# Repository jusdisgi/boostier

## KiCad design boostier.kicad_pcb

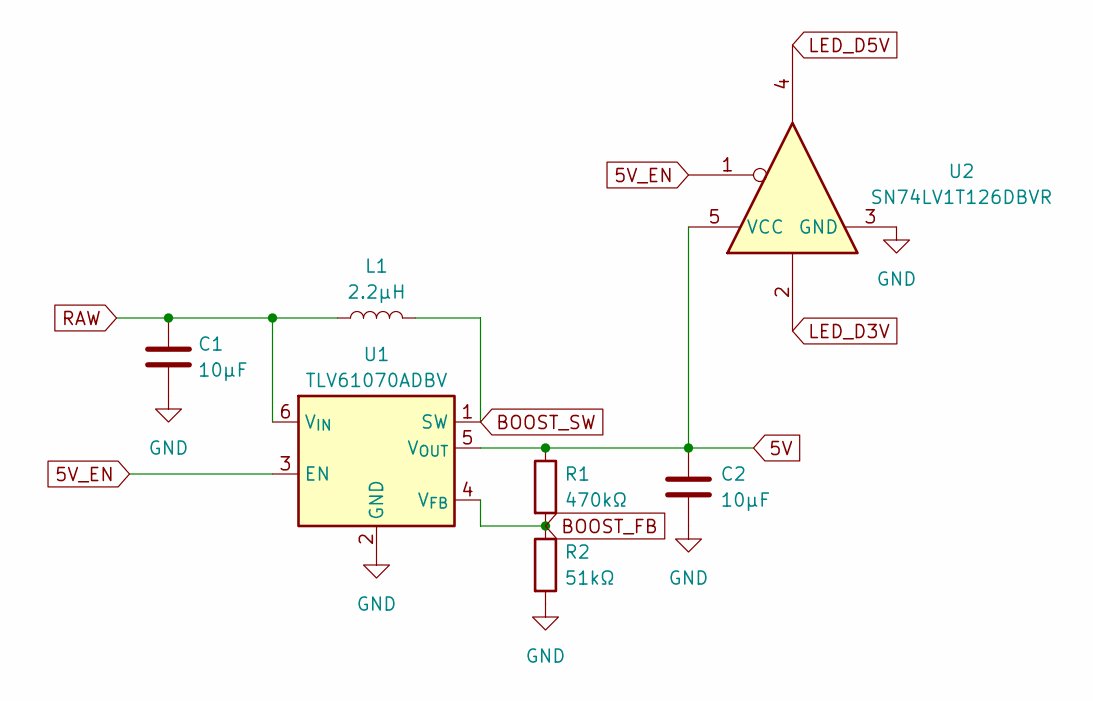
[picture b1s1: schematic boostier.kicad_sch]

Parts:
C1, C2: 10μF; C_0603_1608Metric
L1: 2.2μH; L_CJIANG_FTC404030S_4.1x4.1x3.0_SMD
R1: 470kΩ; R_0603_1608Metric
R2: 51kΩ; R_0603_1608Metric
U1: TLV61070ADBV; SOT-23-6
U2: SN74LV1T126DBVR; SOT-23-5

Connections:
5V: C2.1, R1.1, U1.5 (V_{OUT}), U2.5 (VCC)
5V_EN: U1.3 (EN), U2.1
BOOST_FB: R1.2, R2.1, U1.4 (V_{FB})
BOOST_SW: L1.2, U1.1 (SW)
GND: C1.2, C2.2, R2.2, U1.2 (GND), U2.3 (GND)
LED_D3V: U2.2
LED_D5V: U2.4
RAW: C1.1, L1.1, U1.6 (V_{IN})

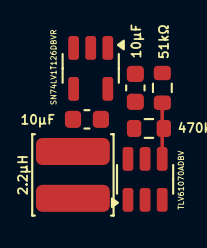
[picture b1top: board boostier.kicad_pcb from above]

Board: 2 copper layers, 7 parts (0 on the bottom side), 6 nets.

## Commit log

2025-06-05 Initial commit, schematic and PCB upload.
2025-06-05 Minor cleanup.
2025-06-05 Cleanup schematic/PCB mismatching net names
2025-06-05 Add gitignore to cull backups and cruft.
2025-06-06 Cleanup.
